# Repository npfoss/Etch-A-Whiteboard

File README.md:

# Etch-A-Whiteboard
Designed, built, coded, tested, and debugged by Nate Foss and Alex Hoganson in the Thomas Jefferson High School for Science and Technology Robotics Senior Tech Lab.

## Documentation
[Hackster.io writeup](https://www.hackster.io/wait-for-it/etch-a-whiteboard-automated-precision-drawing-b8f5b8)

[YouTube playlist of time-lapse videos](https://www.youtube.com/playlist?list=PLRdDXuANN3XmfM99mHG94mfGR06Hm311h)

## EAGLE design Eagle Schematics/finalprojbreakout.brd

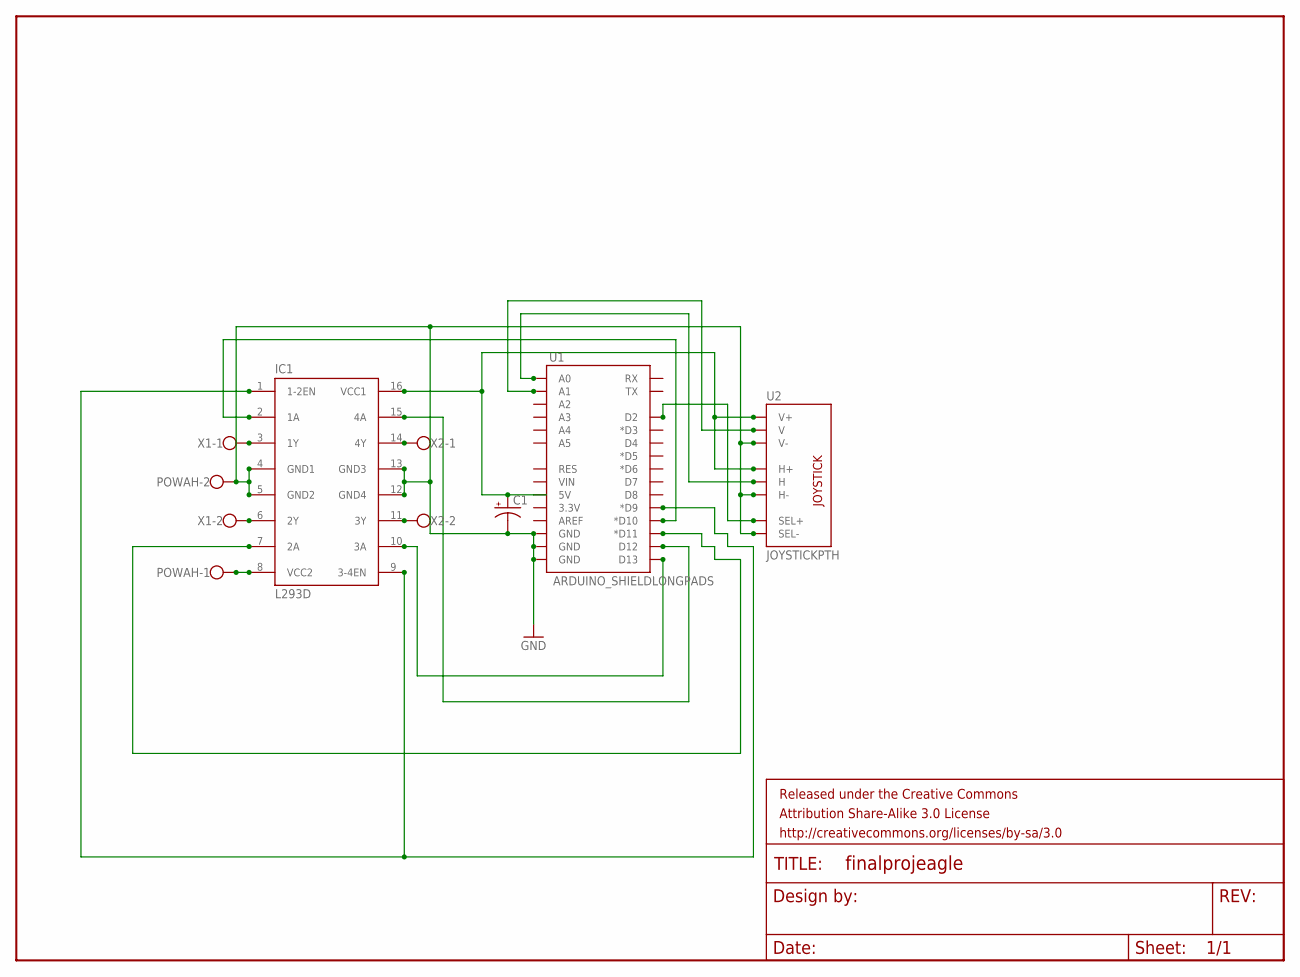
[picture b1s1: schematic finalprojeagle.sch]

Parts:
C1: CAP_POLPTH2; CPOL-RADIAL-10UF-25V
FRAME1: FRAME-LETTER; CREATIVE_COMMONS
IC1: L293D; DIL16
POWAH: W237-102
U1: ARDUINO_SHIELDLONGPADS; DUEMILANOVE_SHIELD_LONGPADS
U2: JOYSTICKPTH; JOYSTICK
X1, X2: W237-102

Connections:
GND: C1.2 (-), IC1.4 (GND1), IC1.5 (GND2), IC1.12 (GND4), IC1.13 (GND3), POWAH.2, U1.GND@0 (GND), U1.GND@1 (GND), U1.GND@2 (GND), U2.B2A (SEL-), U2.H3 (H-), U2.V3 (V-)
unnamed: IC1.8 (VCC2), POWAH.1
unnamed: IC1.3 (1Y), X1.1
unnamed: IC1.6 (2Y), X1.2
unnamed: IC1.14 (4Y), X2.1
unnamed: IC1.11 (3Y), X2.2
unnamed: U1.A1, U2.V2 (V)
unnamed: U1.A0, U2.H2 (H)
unnamed: U1.D2, U2.B1A (SEL+)
unnamed: IC1.2 (1A), U1.D10 (*D10)
unnamed: IC1.1 (1-2EN), IC1.9 (3-4EN), U1.D9 (*D9)
unnamed: IC1.7 (2A), U1.D11 (*D11)
unnamed: IC1.15 (4A), U1.D12
unnamed: IC1.10 (3A), U1.D13
VCC: C1.1 (+), IC1.16 (VCC1), U1.5V, U2.H1 (H+), U2.V1 (V+)

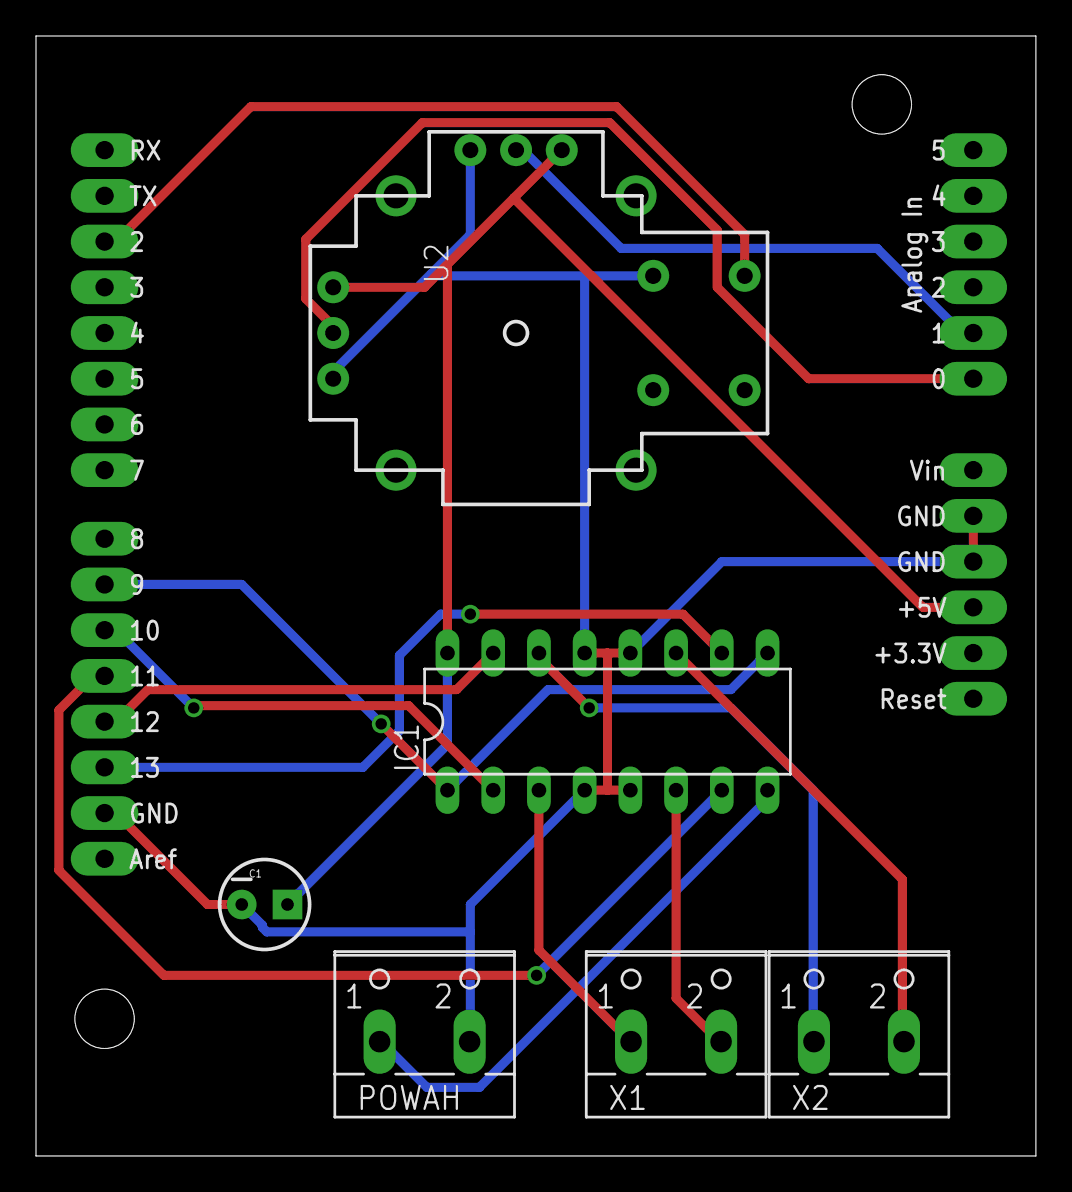
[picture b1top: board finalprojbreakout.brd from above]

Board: 2 copper layers, 55.5 x 62.2 mm, 8 parts (0 on the bottom side), 15 nets.

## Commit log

2015-09-08 :circus_tent: Added .gitattributes
2015-09-08 add all files
2015-09-21 order belts and pulleys
2015-09-24 Changed stuff
2015-09-24 finish overview
2015-09-24 Overview Sheet
2015-09-24 fix things
2015-09-24 not much
2015-10-01 completed CAD of the acrylic inner shield
    cad
2016-03-17 Spring cleaning
2016-03-17 Add all the new CAD files
2016-03-17 how to git
2016-03-19 process first image on rasPi!
2016-03-19 process YTJMIT@
2016-03-29 make a penholder holder
2016-04-01 add delrin sleeves dwg
2016-04-06 started starting to code a starter program, just to start things off
2016-04-11 finish IO tester program, still need to calibrate through trial and error
2016-04-12 test all directions successfully
2016-04-21 fix order of stepper triggers
2016-05-16 start making collar for new top stepper
2016-05-16 new delrin pieces for new steppers
2016-05-26 lots more code, still incomplete
2016-05-31 finish movement resources
2016-05-31 add support for diagonal lines, create test file to draw an octagon, and finish simple driver to interpret instruction file
2016-06-01 finished interpretation side?
2016-06-01 bugfix
2016-06-01 typo
2016-06-01 add call to main you idiot :P
2016-06-02 corrected horizontal movement (it was backwards)
2016-06-02 finish image transforms and instrcution file generation
2016-06-02 minor tweaks
2016-06-02 add tjstar logo image file
2016-06-02 tjstar instruction file
2016-06-04 reconciled this repo with files on syslab computers: all up to date
2016-06-09 add more descriptive headers
2016-06-15 hopefully less wobbly gear
2016-06-15 nothing?
2016-06-16 faster pen
2016-06-19 reconcile with syslab and add file for YouTube video links
2016-06-19 add video links
2016-06-19 reformat readme
2016-06-19 add code to list
    I also coded stuff oops
2016-06-19 eagle files weren't even used in the final version
2016-06-20 add a bash file to make things easier. calculate pixle size intelligently.
2016-08-02 I am so bad at git
2016-08-09 add darth vader drawing to try
2016-08-09 IMAGES
2016-08-09 MORE PICTURES
2016-08-09 mass convert to ppm
2016-08-09 turn into ppm
2016-08-09 make edge finding greedy and generate ytjmit eaw
2016-08-09 undo cleverness--it didn't work
2016-08-10 add more progress indicators
2017-07-21 moving video links to readme
2017-07-21 add videos to readme
2017-07-21 reword readme and remove formatting error

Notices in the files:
parts and their libraries:
SparkFun-Aesthetics: Licensing: CC v3.0 Share-Alike You are welcome to use this library for commercial purposes.
SparkFun-Aesthetics: Released under the Creative Commons Attribution Share-Alike 3.0 License
SparkFun-Aesthetics: http://creativecommons.org/licenses/by-sa/3.0
